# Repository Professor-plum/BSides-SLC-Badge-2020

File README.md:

# BSides-SLC-Badge-2020
Source code, design files, artwork, resoources and 3D printer models used in the BSides SLC 2020 badge

Hardware schematics were design using Eagle
Firmware was compiled using STM32CubeIDE

Programming was done using a ST-link v2 and a USB-TTY tool.# BSides-SLC-Badge-2020
Source code, design files, artwork, resoources and 3D printer models used in the BSides SLC 2020 badge

Hardware schematics were design using Eagle
Firmware was compiled using STM32CubeIDE
All artwork is in the images folder
There are a few scripts inside the resources folder which were used to compile the flash image and program the badges

Programming was done using a ST-link v2 and a USB-TTY tool.

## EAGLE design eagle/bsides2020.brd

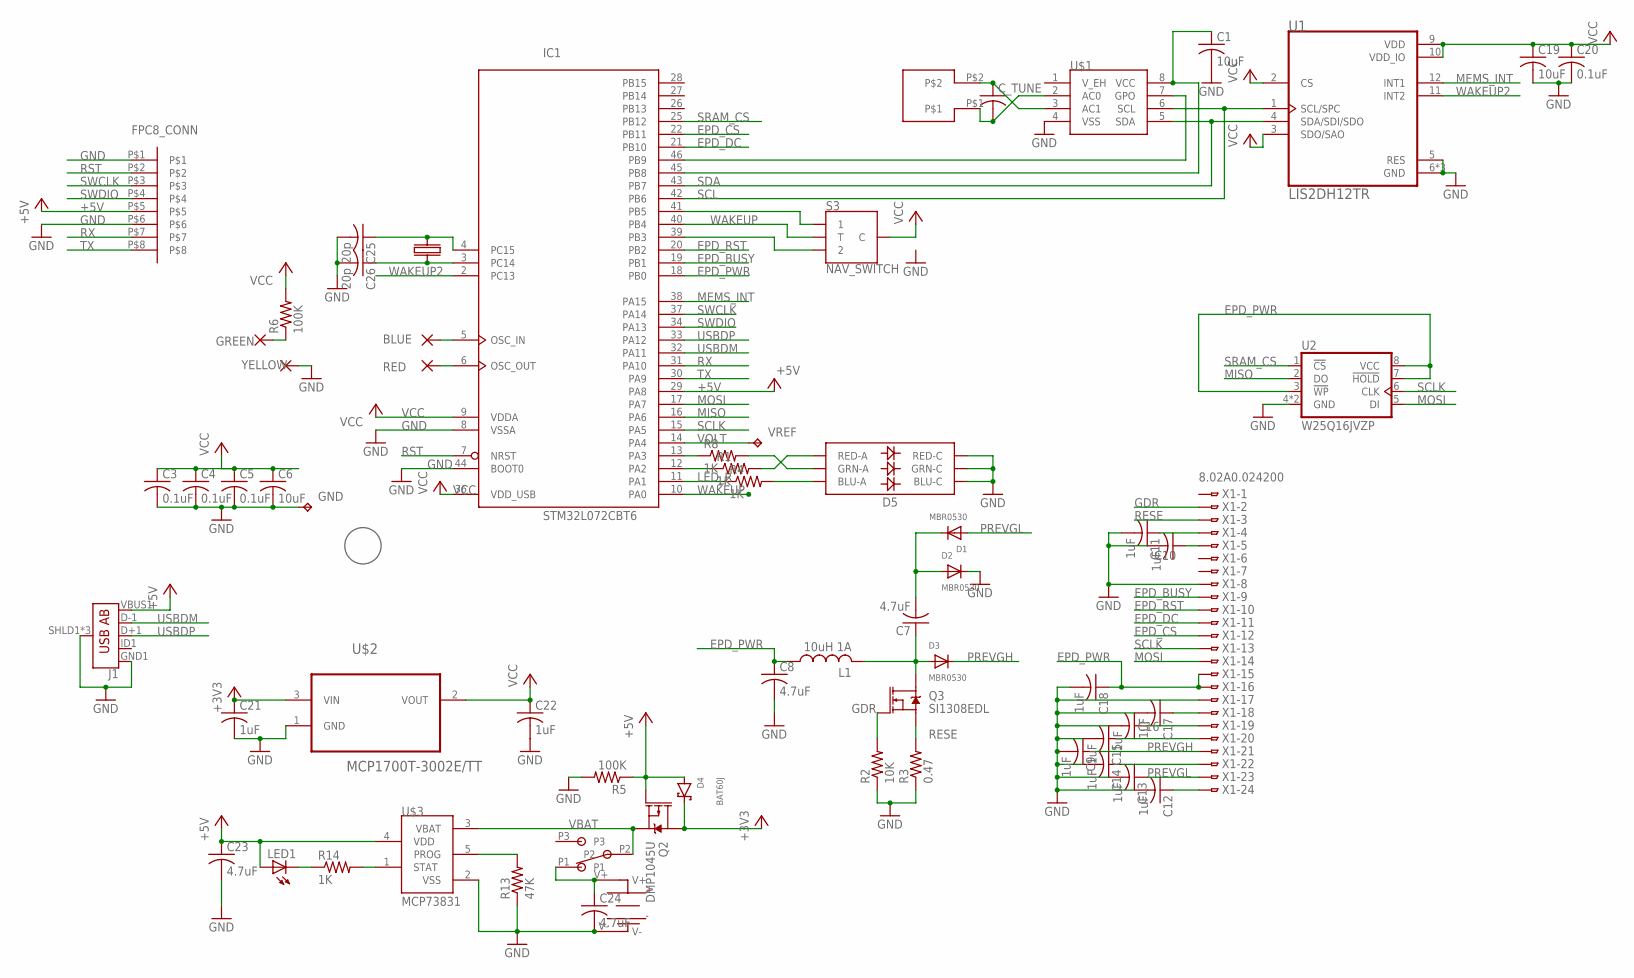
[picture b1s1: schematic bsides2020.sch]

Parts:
BLUE: SMD2; SMD1,27-2,54
C1, C6, C19: 10uF; C0603
C3, C4, C5, C20: 0.1uF; C0603
C7, C8, C23, C24: 4.7uF; C0603
C9, C10, C11, C12, C13, C14, C15, C16, C17, C18, C21, C22: 1uF; C0603
C25, C26: 20p; C0603
C_TUNE: C-USC0603; C0603
D1, D2, D3: MBR0530; SOD-123
D4: BAT60J; SOD323_ST
D5: RGB; LED-TRICOLOR-5050
GND: TPB1,27; B1,27
GREEN: SMD2; SMD1,27-2,54
IC1: STM32L072CBT6; LQFP48
J1: USB_AB_SMT; USB-AB-MICRO-SMD
L1: 10uH 1A; L2825P
LED1: LEDCHIPLED_0603; CHIPLED_0603
Q2: DMP1045U; SOT23-3
Q3: SI1308EDL; SOT23-3
R1, R4, R8, R14: 1K; R0603
R2: 10K; R0603
R3: 0.47; R0603
R5, R6: 100K; R0603
R13: 47K; R0603
RED: SMD2; SMD1,27-2,54
S3: NAV_SWITCH
U1: LIS2DH12TR; LGA-12N
U2: W25Q16JVZP; WSON8
U$1: ST25DV04K-IER6S3; SOIC127P600X175-8N
U$2: MCP1700T-3002E/TT; SOT95P237X112-3N
U$3: MCP73831; SOT23-5L
U$4: ANTANT2; ANT2
U$6: 20MM_BATTERY180; 20MM_BATTERY_SMD2
U$7: FPC8_END
U$8: PLUM
U$9: MSK12C02
U$11: MC-306 32.7680K-A0:ROHS; 32KHZCRYSTAL
VREF: TPB1,27; B1,27
X1: 8.02A0.024200; FPC24
YELLOW: SMD2; SMD1,27-2,54

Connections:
+3V3: C21.1, D4.C, Q2.3 (D), U$2.3 (VIN)
+5V: C23.1, D4.A, IC1.29 (PA8), J1.VBUS1 (VBUS), LED1.A, Q2.1 (G), R5.1, U$3.4 (VDD), U$7.P$5
EPD_BUSY: IC1.19 (PB1), X1.P$9
EPD_CS: IC1.22 (PB11), X1.P$12
EPD_DC: IC1.21 (PB10), X1.P$11
EPD_PWR: C8.1, C18.1, IC1.18 (PB0), L1.1, U2.3 (!WP!), U2.7 (!HOLD!), U2.8 (VCC), X1.P$15, X1.P$16
EPD_RST: IC1.20 (PB2), X1.P$10
GDR: Q3.1 (G), R2.2, X1.P$2
GND: C1.2, C3.2, C4.2, C5.2, C6.2, C8.2, C9.2, C10.2, C11.2, C12.2, C13.2, C14.2, C15.2, C16.2, C17.2, C18.2, C19.2, C20.2, C21.2, C22.2, C23.2, C24.2, C25.2, C26.2, D2.C, D5.4 (BLU-C), D5.5 (RED-C), D5.6 (GRN-C), GND.TP, IC1.8 (VSSA), IC1.23 (VSS), IC1.35 (VSS), IC1.44 (BOOT0), IC1.47 (VSS), J1.GND1 (GND), J1.SHLD1 (SHIELD), J1.SHLD2 (SHIELD), J1.SHLD3 (SHIELD), R2.1, R3.1, R5.2, R13.1, U1.5 (RES), U1.6 (GND), U1.7 (GND), U1.8 (GND), U2.4 (GND), U2.9 (GND), U$1.4 (VSS), U$2.1 (GND), U$3.2 (VSS), U$6.V-, U$7.P$1, U$7.P$6, X1.P$8, X1.P$17, YELLOW.1
LED_R: IC1.11 (PA1), R4.1
MEMS_INT: IC1.38 (PA15), U1.12 (INT1)
MISO: IC1.16 (PA6), U2.2 (DO)
MOSI: IC1.17 (PA7), U2.5 (DI), X1.P$14
unnamed: R13.2, U$3.5 (PROG)
unnamed: BLUE.1, IC1.5 (OSC_IN)
unnamed: D5.2 (RED-A), R1.2
unnamed: D5.1 (GRN-A), R8.2
unnamed: D5.3 (BLU-A), R4.2
unnamed: IC1.41 (PB5), S3.1
unnamed: C24.1, U$6.V+, U$9.P1
unnamed: C26.1, IC1.3 (PC14), U$11.P$4
unnamed: IC1.46 (PB9), U$1.7 (GPO)
unnamed: C_TUNE.2, U$1.2 (AC0), U$4.P$1
unnamed: C11.1, X1.P$4
unnamed: IC1.39 (PB3), S3.2
unnamed: IC1.12 (PA2), R1.1
unnamed: IC1.13 (PA3), R8.1
unnamed: C25.1, IC1.4 (PC15), U$11.P$1
unnamed: C7.1, D3.A, L1.2, Q3.3 (D)
unnamed: C10.1, X1.P$5
unnamed: IC1.6 (OSC_OUT), RED.1
unnamed: C1.1, IC1.45 (PB8), U$1.8 (VCC)
unnamed: C16.1, X1.P$19
unnamed: C15.1, X1.P$20
unnamed: C17.1, X1.P$18
unnamed: C14.1, X1.P$22
unnamed: C12.1, X1.P$24
unnamed: GREEN.1, R6.1
unnamed: C7.2, D1.C, D2.A
unnamed: C_TUNE.1, U$1.3 (AC1), U$4.P$2
unnamed: LED1.C, R14.1
unnamed: R14.2, U$3.1 (STAT)
PREVGH: C9.1, D3.C, X1.P$21
PREVGL: C13.1, D1.A, X1.P$23
RESE: Q3.2 (S), R3.2, X1.P$3
RST: IC1.7 (NRST), U$7.P$2
RX: IC1.31 (PA10), U$7.P$7
SCL: IC1.42 (PB6), U1.1 (SCL/SPC), U$1.6 (SCL)
SCLK: IC1.15 (PA5), U2.6 (CLK), X1.P$13
SDA: IC1.43 (PB7), U1.4 (SDA/SDI/SDO), U$1.5 (SDA)
SRAM_CS: IC1.25 (PB12), U2.1 (!CS!)
SWCLK: IC1.37 (PA14), U$7.P$3
SWDIO: IC1.34 (PA13), U$7.P$4
TX: IC1.30 (PA9), U$7.P$8
USBDM: IC1.32 (PA11), J1.D-1 (D-)
USBDP: IC1.33 (PA12), J1.D+1 (D+)
VBAT: Q2.2 (S), U$3.3 (VBAT), U$9.P2
VCC: C3.1, C4.1, C5.1, C6.1, C19.1, C20.1, C22.1, IC1.1 (VDD), IC1.9 (VDDA), IC1.24 (VDD), IC1.36 (VDD_USB), IC1.48 (VDD), R6.2, S3.C, U1.2 (CS), U1.3 (SDO/SAO), U1.9 (VDD), U1.10 (VDD_IO), U$2.2 (VOUT)
VOLT: IC1.14 (PA4), VREF.TP
WAKEUP: IC1.10 (PA0), IC1.40 (PB4), S3.T
WAKEUP2: IC1.2 (PC13), U1.11 (INT2)

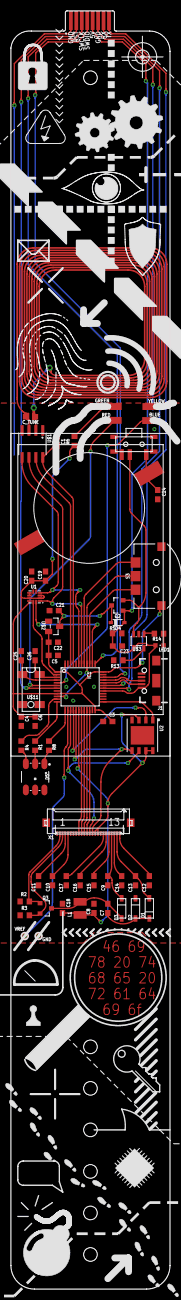
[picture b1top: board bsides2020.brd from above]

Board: 2 copper layers, 29.2 x 234.5 mm, 66 parts (0 on the bottom side), 61 nets.

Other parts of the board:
U$5: EPD_2.13

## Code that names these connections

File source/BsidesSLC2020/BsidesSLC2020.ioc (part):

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PA6.Mode=Full_Duplex_Master
PH0-OSC_IN.GPIO_PuPd=GPIO_PULLDOWN
PH0-OSC_IN.Signal=GPIO_Input
Mcu.UserName=STM32L072CBTx
PB4.GPIO_ModeDefaultEXTI=GPIO_MODE_IT_RISING
PA11.Mode=Device
PH0-OSC_IN.GPIOParameters=GPIO_PuPd,GPIO_Label
PA3.GPIOParameters=GPIO_Label
PB0.GPIO_Label=EPD_PWR
PB3.GPIO_ModeDefaultEXTI=GPIO_MODE_IT_RISING
PB11.Signal=GPIO_Output
PA2.GPIOParameters=GPIO_Label
RCC.SYSCLKSource=RCC_SYSCLKSOURCE_HSI
PB5.GPIOParameters=GPIO_PuPd,GPIO_Label,GPIO_ModeDefaultEXTI
PA15.GPIO_Label=MEMS_INT
PB4.GPIOParameters=GPIO_PuPd,GPIO_Label,GPIO_ModeDefaultEXTI
PA12.Signal=USB_DP
PB0.PinState=GPIO_PIN_SET
PA15.GPIO_ModeDefaultEXTI=GPIO_MODE_IT_FALLING
PB6.Signal=I2C1_SCL
PB6.Mode=I2C
PA8.GPIOParameters=GPIO_Label,GPIO_ModeDefaultEXTI
PB9.GPIO_ModeDefaultEXTI=GPIO_MODE_IT_FALLING
PH0-OSC_IN.GPIO_Label=BLUE
RCC.HSE_VALUE=8000000
PB2.Signal=GPIO_Output
PB12.GPIO_Label=FLASH_CS
PB0.GPIOParameters=PinState,GPIO_Label
PB3.GPIO_PuPd=GPIO_PULLDOWN
PA1.GPIOParameters=GPIO_Label
PC14-OSC32_IN.Mode=LSE-External-Oscillator
PA14.Mode=Serial_Wire
PB1.GPIO_Label=EPD_BUSY
PA0.Mode=SYS_WakeUp0
PB8.PinState=GPIO_PIN_SET
PB3.GPIOParameters=GPIO_PuPd,GPIO_Label,GPIO_ModeDefaultEXTI
PB7.Signal=I2C1_SDA
PA8.Signal=GPXTI8
PA0.Signal=SYS_WKUP1
Mcu.Package=LQFP48
PB9.Signal=GPXTI9
PB1.Signal=GPIO_Input
PA6.Signal=SPI1_MISO
PA8.GPIO_ModeDefaultEXTI=GPIO_MODE_IT_RISING_FALLING
PA2.GPIO_Label=GRN_LED
PA10.Signal=USART1_RX
PB9.GPIO_PuPd=GPIO_PULLUP
PA15.Signal=GPXTI15
PB5.GPIO_Label=BTN_UP
PB10.GPIOParameters=GPIO_Label
PB4.Signal=GPXTI4
PA3.Signal=GPIO_Output
PA5.Mode=Full_Duplex_Master
PB3.GPIO_Label=BTN_DN
PB5.GPIO_ModeDefaultEXTI=GPIO_MODE_IT_RISING
PC15-OSC32_OUT.Mode=LSE-External-Oscillator
PB8.GPIOParameters=PinState,GPIO_Label
PA7.Mode=Full_Duplex_Master
PB9.GPIO_Label=NFC_INT
PA10.Mode=Asynchronous
PA15.GPIOParameters=GPIO_PuPd,GPIO_Label,GPIO_ModeDefaultEXTI
PC13.Signal=SYS_WKUP2
PB11.GPIO_Label=EPD_CS
PC14-OSC32_IN.Signal=RCC_OSC32_IN
PB9.GPIOParameters=GPIO_PuPd,GPIO_Label,GPIO_ModeDefaultEXTI
PA13.Signal=SYS_SWDIO
PB8.GPIO_Label=NFC_PWR
PA9.Mode=Asynchronous
PA8.GPIO_Label=VBUS
PB10.GPIO_Label=EPD_DC
PB2.GPIOParameters=GPIO_Label
PA9.Signal=USART1_TX
PB11.GPIOParameters=GPIO_Label
PB4.GPIO_PuPd=GPIO_PULLDOWN
PC15-OSC32_OUT.Signal=RCC_OSC32_OUT
PH1-OSC_OUT.GPIO_PuPd=GPIO_PULLUP
PA1.Signal=GPIO_Output
PB10.Signal=GPIO_Output
PA5.Signal=SPI1_SCK
board=custom
PB4.GPIO_Label=BTN
PA1.GPIO_Label=RED_LED
PH1-OSC_OUT.Signal=GPIO_Input
PH1-OSC_OUT.GPIO_Label=RED
PC13.Mode=SYS_WakeUp1
PA13.Mode=Serial_Wire
Mcu.Name=STM32L072C(B-Z)Tx
PA2.Signal=GPIO_Output
PB3.Signal=GPXTI3
PA4.Signal=COMP_DAC1_group
RCC.SYSCLKFreq_VALUE=16000000
PB5.Signal=GPXTI5
PA12.Mode=Device
PB5.GPIO_PuPd=GPIO_PULLDOWN
PH1-OSC_OUT.GPIOParameters=GPIO_PuPd,GPIO_Label
PB7.Mode=I2C
PA11.Signal=USB_DM
PA14.Signal=SYS_SWCLK
PB2.GPIO_Label=EPD_RST
PA15.GPIO_PuPd=GPIO_NOPULL
PB8.Signal=GPIO_Output
PB0.Signal=GPIO_Output
PB12.GPIOParameters=GPIO_Label
PB12.Signal=GPIO_Output
PA3.GPIO_Label=BLU_LED
PB1.GPIOParameters=GPIO_Label
PA7.Signal=SPI1_MOSI

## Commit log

2020-03-17 Initial check in
2021-02-09 Added Presentation slides
2021-02-09 Added presentation deck

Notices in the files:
parts and their libraries:
memory-winbond: Copyright (C) 2010, Bob Starr
SparkFun-Connectors: Licensing: Creative Commons ShareAlike 4.0 International - https://creativecommons.org/licenses/by-sa/4.0
